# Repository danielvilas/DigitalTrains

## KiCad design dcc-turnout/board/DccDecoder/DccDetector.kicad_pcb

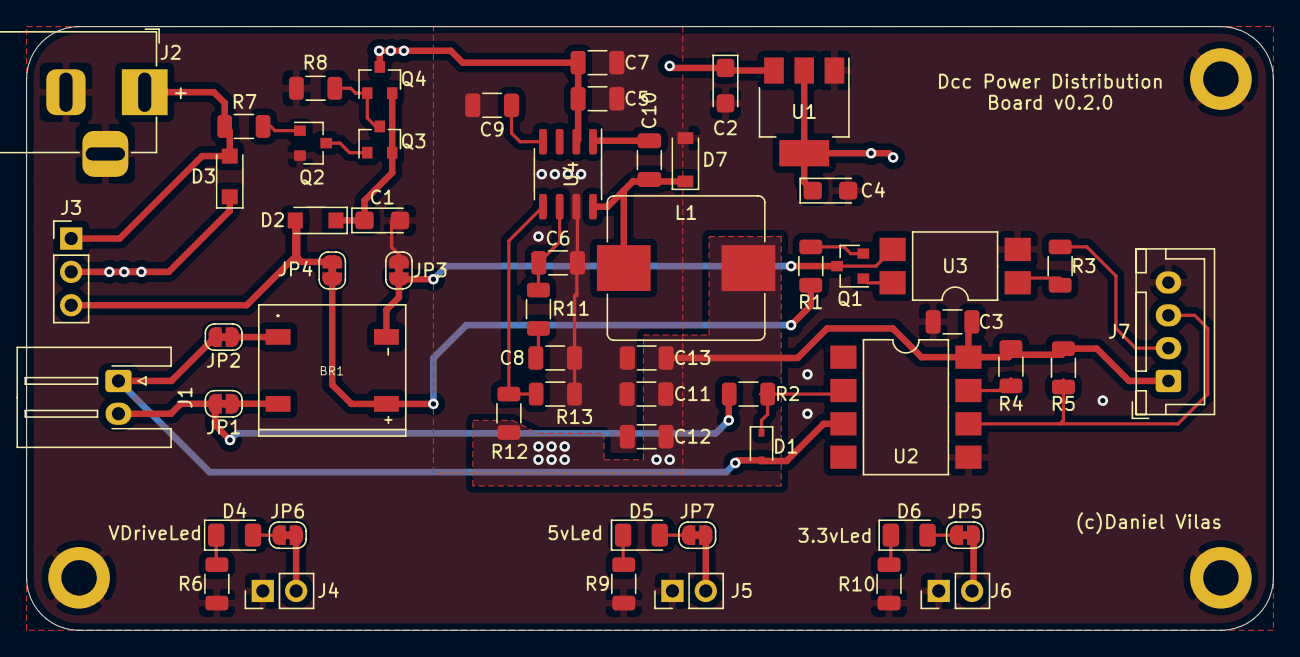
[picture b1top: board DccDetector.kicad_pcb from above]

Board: 4 copper layers, 95.0 x 46.0 mm, 60 parts (0 on the bottom side), 35 nets.

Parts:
BR1: DB107S; DIOB_DB107S
C1, C2, C4: 10uf; CP_EIA-3216-18_Kemet-A
C3: 10uf; C_1206_3216Metric
C5, C7, C11, C12, C13: 10uf 2m; C_1206_3216Metric
C6: 10pf; C_1206_3216Metric
C8: 5.6nf; C_1206_3216Metric
C9: 8.2nf; C_1206_3216Metric
C10: 100nf 1m; C_1206_3216Metric
D1: 1N4148; D_SOD-323
D2, D3: GS1510FL; D_SOD-123FL
D4, D5, D6: LED; LED_1206_3216Metric
D7: SS24A+; D_SOD-123
H1, H2, H3: MountingHole_Pad; MountingHole_2.7mm_M2.5_DIN965_Pad
J1: Conn_01x02; JST_XH_S2B-XH-A-1_1x02_P2.50mm_Horizontal
J2: Conn_01x02; BarrelJack_Horizontal
J3: Conn_01x03; PinHeader_1x03_P2.54mm_Vertical
J4, J5, J6: Conn_01x02; PinHeader_1x02_P2.54mm_Vertical
J7: Conn_01x04; JST_XH_B4B-XH-A_1x04_P2.50mm_Vertical
JP1, JP2, JP3, JP4: Jumper_NC; SolderJumper-2_P1.3mm_Bridged_RoundedPad1.0x1.5mm
JP5, JP6, JP7: Jumper_2_Bridged; SolderJumper-2_P1.3mm_Bridged_RoundedPad1.0x1.5mm
L1: 22uH 75mO; L_Bourns_SRP1035
Q1: BC857; SOT-23
Q2: BC817; SOT-23
Q3: BC807; SOT-23
Q4: BSS308; SOT-23
R1, R10: 100; R_1206_3216Metric
R2: 3k; R_1206_3216Metric
R3: 1K; R_1206_3216Metric
R4, R5: 10K; R_1206_3216Metric
R6: 900; R_1206_3216Metric
R7, R8: 100K; R_1206_3216Metric
R9: 200; R_1206_3216Metric
R11: 5.62K; R_1206_3216Metric
R12: 10.2K; R_1206_3216Metric
R13: 1.96K; R_1206_3216Metric
U1: AMS1117-3.3; SOT-223-3_TabPin2
U2: 6N137S1; SMDIP-8_W9.53mm
U3: PC817; SMDIP-4_W9.53mm
U4: TPS54331D; SOIC-8_3.9x4.9mm_P1.27mm

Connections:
+3V3: C4.1, J6.2, JP5.2, U1.2
+5V: C2.1, C3.1, C11.1, C12.1, C13.1, J5.2, J7.1, JP7.2, L1.2, R4.2, R5.2, R12.1, U1.3, U2.8
/Dcc Interface/DccP+: BR1.+, JP4.1, R1.2
/Dcc Interface/DccP-: BR1.-, JP3.1, Q1.3, U3.3
/Dcc Interface/DccPower: D2.2, J3.3, JP4.2
/Dcc Interface/J: J1.2, JP1.2, R2.2
/Dcc Interface/J_ACK: BR1.~, JP1.1
/Dcc Interface/K: D1.2, J1.1, JP2.2, U2.3
/Dcc Interface/K_ACK: BR1.~., JP2.1
/Power Distribution/Vin: D3.2, J2.1, J3.1, R7.2
/Power Distribution/_BOOT: C10.1, U4.1
/Power Distribution/_DccVinP: C1.1, D2.1, Q3.2, Q4.2
/Power Distribution/_PH: C10.2, D7.1, L1.1, U4.8
/_ack: J7.2, R3.1
/_dcc: J7.3, R5.1, U2.6
GND: C1.2, C2.2, C3.2, C4.2, C5.2, C6.2, C7.2, C8.2, C9.2, C11.2, C12.2, C13.2, D7.2, H1.1, H2.1, H3.1, J2.2, J2.3, J4.1, J5.1, J6.1, J7.4, JP3.2, Q2.2, R6.2, R8.2, R9.2, R10.2, R13.2, U1.1, U2.5, U3.2, U4.7
unnamed: C6.1, R11.1, U4.6
unnamed: C8.1, R11.2
unnamed: C9.1, U4.4
unnamed: D1.1, R2.1, U2.2
unnamed: D4.1, R6.1
unnamed: D4.2, JP6.1
unnamed: D5.1, R9.1
unnamed: D5.2, JP7.1
unnamed: D6.1, R10.1
unnamed: D6.2, JP5.1
unnamed: Q1.1, U3.4
unnamed: Q1.2, R1.1
unnamed: Q2.1, R7.1
unnamed: Q2.3, Q3.1
unnamed: Q3.3, Q4.1, R8.1
unnamed: R3.2, U3.1
unnamed: R4.1, U2.7
unnamed: R12.2, R13.1, U4.5
Vdrive: C5.1, C7.1, D3.1, J3.2, J4.2, JP6.2, Q4.3, U4.2

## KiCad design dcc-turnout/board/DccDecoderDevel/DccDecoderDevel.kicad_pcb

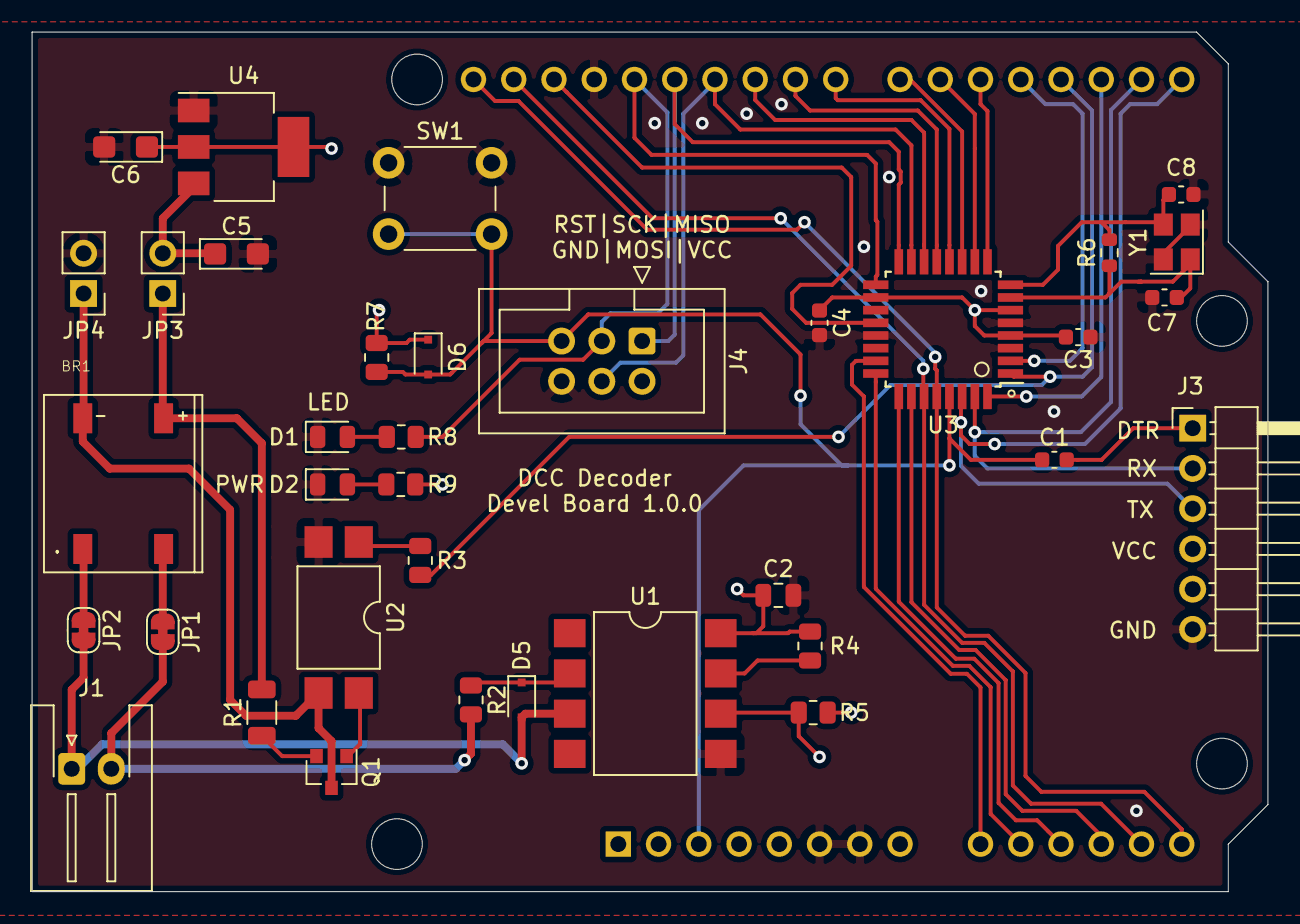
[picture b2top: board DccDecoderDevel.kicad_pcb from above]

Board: 4 copper layers, 78.0 x 54.2 mm, 37 parts (1 on the bottom side), 41 nets.

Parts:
A1: Arduino_UNO_R3; Arduino_UNO_R3_WithMountingHoles
BR1: DB107S; DIOB_DB107S
C1, C3, C4: 100nf; C_0603_1608Metric
C2: 10uf; C_0805_2012Metric
C5, C6: 10uf; CP_EIA-3216-18_Kemet-A
C7, C8: 22pf; C_0603_1608Metric
D1, D2: LED; LED_0805_2012Metric
D5: 1N4148; D_SOD-323F
D6: CD1206-S01575; D_SOD-323F
J1: Conn_01x02; JST_XH_S2B-XH-A-1_1x02_P2.50mm_Horizontal
J3: Conn_01x06; PinHeader_1x06_P2.54mm_Horizontal
J4: ICSP; IDC-Header_2x03_P2.54mm_Vertical
JP1, JP2: Jumper_NC_Small; SolderJumper-2_P1.3mm_Bridged_RoundedPad1.0x1.5mm
JP3, JP4: Jumper_NO; PinHeader_1x02_P2.54mm_Vertical
Q1: BC560; SOT-23
R1: 100; R_1206_3216Metric
R2: 3k; R_0805_2012Metric
R3: 1K; R_0805_2012Metric
R4, R5, R7, R8, R9: 10K; R_0805_2012Metric
R6: 1M; R_0603_1608Metric
SW1: SW_Push; SW_PUSH_6mm_H4.3mm
U1: 6N137; SMDIP-8_W9.53mm
U2: PC817; SMDIP-4_W9.53mm
U3: ATmega328P-AU; TQFP-32_7x7mm_P0.8mm
U4: AMS1117-5.0; SOT-223-3_TabPin2
Y1: Crystal_GND24; Crystal_SMD_3225-4Pin_3.2x2.5mm

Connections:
+12V: A1.8, C5.1, JP3.2, U4.3
/A0: A1.9, U3.23
/A1: A1.10, U3.24
/A2: A1.11, U3.25
/A3: A1.12, U3.26
/A4: A1.13, A1.31, U3.27
/A5: A1.14, A1.32, U3.28
/AREF: A1.30, U3.20
/D2: A1.17, R5.1, U1.6, U3.32
/D3: A1.18, R3.1, U3.1
/D4: A1.19, U3.2
/D5: A1.20, U3.9
/D6: A1.21, U3.10
/D7: A1.22, U3.11
/D8: A1.23, U3.12
/D9: A1.24, U3.13
/D10: A1.25, U3.14
/D11: A1.26, J4.4, U3.15
/D12: A1.27, J4.1, U3.16
/D13: A1.28, J4.3, R8.2, U3.17
/DTR: C1.2, J3.1
/Dcc-Interface/DCC_A: J1.2, JP1.2, R2.2
/Dcc-Interface/DCC_B: D5.2, J1.1, JP2.2, U1.3
/Dcc-Interface/J_ACK: BR1.~, JP1.1
/Dcc-Interface/K_ACK: BR1.~., JP2.1
/FTDI_RX: A1.16, J3.2, U3.31
/FTDI_TX: A1.15, J3.3, U3.30
/RST: A1.3, C1.1, D6.2, J4.5, R7.2, SW1.2, U3.29
GND: A1.6, A1.7, A1.29, C2.2, C3.1, C4.2, C5.2, C6.2, C7.1, C8.1, D1.1, D2.1, J3.6, J4.6, JP4.2, SW1.1, U1.5, U2.2, U3.3, U3.5, U3.21, U4.1, Y1.2, Y1.4
unnamed: BR1.+, JP3.1, R1.2
unnamed: BR1.-, JP4.1, Q1.3, U2.3
unnamed: C7.2, R6.1, U3.7, Y1.1
unnamed: C8.2, R6.2, U3.8, Y1.3
unnamed: D1.2, R8.1
unnamed: D2.2, R9.1
unnamed: D5.1, R2.1, U1.2
unnamed: Q1.1, U2.4
unnamed: Q1.2, R1.1
unnamed: R3.2, U2.1
unnamed: R4.1, U1.7
VCC: A1.2, A1.5, C2.1, C3.2, C4.1, C6.1, D6.1, J3.4, J4.2, R4.2, R5.2, R7.1, R9.2, U1.8, U3.4, U3.6, U3.18, U4.2

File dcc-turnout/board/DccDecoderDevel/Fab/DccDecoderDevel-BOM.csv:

Comment,Designator,Footprint,LCSC, LCSC, MANUFACTURER
"Arduino_UNO_R3","A1","Module:Arduino_UNO_R3_WithMountingHoles",""
"DB107S","BR1","Project:DIOB_DB107S","","C5377","Rectron Semiconductor"
"100nf","C1,C4,C3","Capacitor_SMD:C_0603_1608Metric","","C14663",""
"10uf","C2","Capacitor_SMD:C_0805_2012Metric","","C15850",""
"10uf","C6,C5","Capacitor_Tantalum_SMD:CP_EIA-3216-18_Kemet-A",""," C7171",""
"22pf","C7,C8","Capacitor_SMD:C_0603_1608Metric","","C1653",""
"LED","D2,D1","LED_SMD:LED_0805_2012Metric","","C2296",""
"1N4148","D5","Diode_SMD:D_SOD-323F","","C2128",""
"CD1206-S01575","D6","Diode_SMD:D_SOD-323F",""," C2128",""
"Conn_01x02","J1","Connector_JST:JST_XH_S2B-XH-A-1_1x02_P2.50mm_Horizontal",""
"Conn_01x06","J3","Connector_PinHeader_2.54mm:PinHeader_1x06_P2.54mm_Horizontal",""
"ICSP","J4","Connector_IDC:IDC-Header_2x03_P2.54mm_Vertical",""
"Jumper_NC_Small","JP1,JP2","Jumper:SolderJumper-2_P1.3mm_Bridged_RoundedPad1.0x1.5mm",""
"Jumper_NO","JP4,JP3","Connector_PinHeader_2.54mm:PinHeader_1x02_P2.54mm_Vertical",""
"BC560","Q1","Package_TO_SOT_SMD:SOT-23","","C8326",""
"100","R1","Resistor_SMD:R_1206_3216Metric","","C17901",""
"3k","R2","Resistor_SMD:R_0805_2012Metric","","C17661",""
"1K","R3","Resistor_SMD:R_0805_2012Metric","","C17513",""
"1M","R6","Resistor_SMD:R_0603_1608Metric",""," C22935",""
"10K","R9,R8,R4,R5,R7","Resistor_SMD:R_0805_2012Metric","","C17414",""
"SW_Push","SW1","Button_Switch_THT:SW_PUSH_6mm_H4.3mm",""
"6N137","U1","Package_DIP:SMDIP-8_W9.53mm","","C110020",""
"PC817","U2","Package_DIP:SMDIP-4_W9.53mm","","C106900",""
"ATmega328P-AU","U3","Project:TQFP-32_7x7mm_P0.8mm","","C14877",""
"AMS1117-5.0","U4","Package_TO_SOT_SMD:SOT-223-3_TabPin2","","C6187",""
"Crystal_GND24","Y1","Crystal:Crystal_SMD_3225-4Pin_3.2x2.5mm","","C13738",""

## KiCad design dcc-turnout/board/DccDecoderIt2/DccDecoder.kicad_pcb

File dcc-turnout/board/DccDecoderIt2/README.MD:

# Dcc Decoder
This is a Dcc Decoder Module to move a turnout with a Servo

> __WARN__: this folder is a second iteration, to try to model PCB different. and check with version is more addecuate
>
> After testing some iterations only one will be on the repository.

## Desired Specs Status
* ̣[x]Remove Power Distribution to project:  [Power Distribution](../DccBlocks/DccPowerDistribution/)
* [ ] 2 Outputs for LEDs Aspects, to Vin
* [ ] 1 Rele Ouput (5V or 0)
* [x] UART for advanced configuration
* [x] Configure Pins
  * [ ] CV Program to advanced CF
    * [ ] POM if possible
  * [ ] Config mode to capture dcc Address
  * [x] Advanced config mode (2 packets, CV, value)
* [x] Reset Button
* [x] Programing port
  * [ ] Bootloader for uart if possible
  * [ ] if possible no BootX pins
* [x] I2C for EzyBus

## Power Design
First is to determine the power requirments of the diferent main sections, wihch are:

|       |min|expected|max|notes|
|---    |--:|--:|--:|---|
|Servo  | 5 |150|800|idle, run, stall|
|Leds   |10 |20 |40 | underlight, 1led, Both|
|Rele   |0  |80 |100| off, std, +margins|
|MCU    |20 |80 |120|STM32 minum, arduino expected[(1)](https://www.gadgetmakersblog.com/power-consumption-arduinos-atmega328-microcontroller/), +margin|
|Others |10|50|60| extra margins
|**Sum**|45|**380**|*1020*|

In the reality, the max compsution of the servo (Stall) may only occurr when the user is setting up the device. So with this information we can design our power stage, from VDrive to 5V using "WEBENCH Power Designer" indicating we want **1 AMP output** wiht nominal output of **500mA**

## ChangeLog
### v0.1.0
* Initial Version
### v0.2.0
* [x] Buck Converter
* [x] Power Switch with mosfet
### v0.3.0
* [X] D1 FootPrint
* [x] D7 Check stock and review footprint
* [x] Output Connectors, following amps and voltage
* [x] Check 12v DC Jack size with layout
* [X] J7 (Dcc iface) horizontal
* [X] J7 Silk explanation
* [x] J1,J2 and J3, place a bit low and add Mount Hole
* [x] J1,J2 and J3, explain in silk.
* [x] JP* (all) explain in silk (back)
* [x] Dcc iface add jumper Normally Open to isolate 5v rail from buck
* [x] Copy design to new Project (Dcc Power Distributor)
## v0.4.0
* [x] Remove Power Distritubion
* [x Basic MCU
  * [x] MCU
  * [x] SWD
  * [x] Boot 0
* [x] UART.
* [x] I2C
* [x] LEDS
* [x] RELE
* [x] Servo
  * [ ] full
  * [x] enabled
* [x] Config Pins

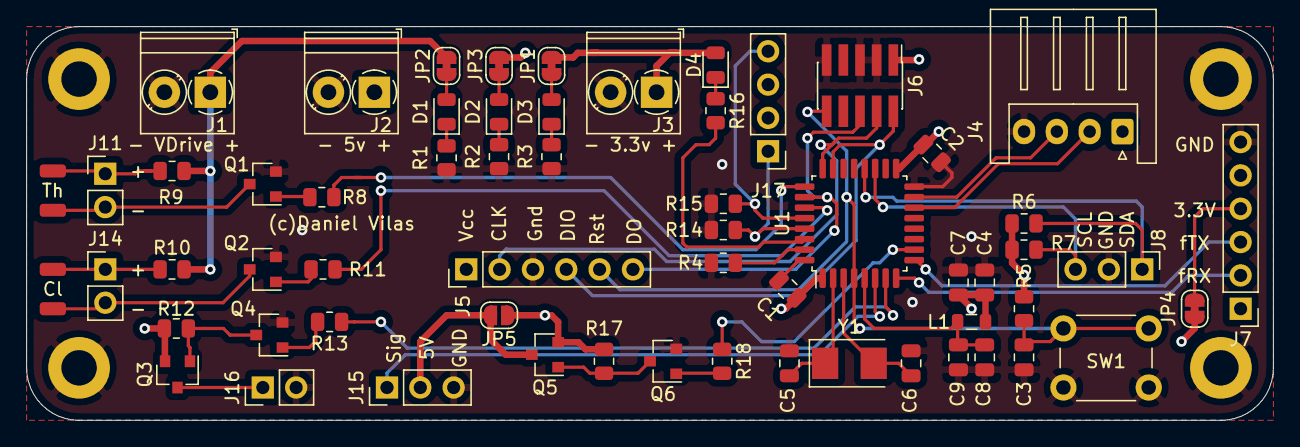
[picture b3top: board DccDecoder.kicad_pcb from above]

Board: 4 copper layers, 95.0 x 30.0 mm, 67 parts (0 on the bottom side), 46 nets.

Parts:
C1, C2, C3: 100nf; C_0805_2012Metric
C4, C8: 1uF; C_0805_2012Metric
C5, C6: 20pf; C_0805_2012Metric
C7, C9: 10nF; C_0805_2012Metric
D1, D2, D3, D4: LED; LED_0805_2012Metric
H1, H2, H3, H4: MountingHole_Pad; MountingHole_2.7mm_M2.5_DIN965_Pad
J1, J2, J3: Conn_01x02; TerminalBlock_Phoenix_PT-1,5-2-3.5-H_1x02_P3.50mm_Horizontal
J4: Conn_01x04; JST_XH_S4B-XH-A_1x04_P2.50mm_Horizontal
J5, J7: Conn_01x06; PinHeader_1x06_P2.54mm_Vertical
J6: Conn_02x05 Odd_Even; PinHeader_2x05_P1.27mm_Vertical_SMD
J8, J15: Conn_01x03; PinHeader_1x03_P2.54mm_Vertical
J9, J10, J12, J13: Conn_01x01; SolderWirePad_1x01_SMD_1x2mm
J11, J14, J16: Conn_01x02; PinHeader_1x02_P2.54mm_Vertical
J17: Conn_01x04; PinHeader_1x04_P2.54mm_Vertical
JP1, JP2, JP3, JP4: Jumper_2_Bridged; SolderJumper-2_P1.3mm_Bridged_RoundedPad1.0x1.5mm
JP5: Jumper_2_Open; SolderJumper-2_P1.3mm_Open_RoundedPad1.0x1.5mm
L1: 10uH; L_0805_2012Metric
Q1, Q2, Q4, Q6: AO3400A; SOT-23
Q3, Q5: AO3401A; SOT-23
R1, R6, R7, R8, R9, R10, R11, R12, R13, R14, R15, R17, R18: 1K; R_0805_2012Metric
R2: 200; R_0805_2012Metric
R3, R16: 100; R_0805_2012Metric
R4, R5: 10K; R_0805_2012Metric
SW1: SW_Push; SW_PUSH_6mm
U1: STM32F030K6Tx; LQFP-32_7x7mm_P0.8mm
Y1: 8MHz; Crystal_SMD_5032-2Pin_5.0x3.2mm

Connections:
+3V3: C1.2, C2.2, C4.1, C7.1, D4.2, J3.1, J5.1, J6.1, J17.2, J17.3, JP1.2, JP4.2, L1.2, R5.1, R6.1, R7.1, U1.1, U1.17
+5V: J2.1, J4.1, JP3.2, JP5.1, Q3.2, Q5.2, R12.2, R17.2
/CfgAdvanced: J17.4, R15.2, U1.28
/CfgBasic: J17.1, R14.2, U1.29
/CfgStatus: R16.2, U1.30
/ClosedLed: R11.1, U1.27
/F_RX: J7.2, U1.8
/F_TX: J7.3, U1.9
/F_Vcc: J7.4, JP4.1
/Out Puts/_ServoPwr: J15.2, JP5.2, Q5.3
/ReleEn: R13.1, U1.7
/SCL: J8.3, R7.2, U1.19
/SDA: J8.1, R6.2, U1.20
/ServoEn: R18.1, U1.10
/ServoSig: J15.1, U1.6
/ThrownLed: R8.1, U1.25
/_ack: J4.2, U1.14
/_dcc: J4.3, U1.15
/uC 030K6/BOOT0: R4.1, U1.31
/uC 030K6/NRST: C3.1, J5.5, J6.10, R5.2, SW1.1, U1.4
/uC 030K6/PA13: J5.4, J6.2, U1.23
/uC 030K6/PA14: J5.2, J6.4, U1.24
/uC 030K6/PB3: J5.6, J6.6, U1.26
/uC 030K6/PF0: C5.1, U1.2, Y1.1
/uC 030K6/PF1: C6.1, U1.3, Y1.2
/uC 030K6/_VDDA: C8.1, C9.1, L1.1, U1.5
GND: C1.1, C2.1, C3.2, C4.2, C5.2, C6.2, C7.2, C8.2, C9.2, H1.1, H2.1, H3.1, H4.1, J1.2, J2.2, J3.2, J4.4, J5.3, J6.3, J6.5, J6.9, J7.6, J8.2, J15.3, J16.2, Q1.2, Q2.2, Q4.2, Q6.2, R1.2, R2.2, R3.2, R4.2, R14.1, R15.1, SW1.2, U1.16, U1.32
unnamed: D1.1, R1.1
unnamed: D1.2, JP2.1
unnamed: D2.1, R2.1
unnamed: D2.2, JP3.1
unnamed: D3.1, R3.1
unnamed: D3.2, JP1.1
unnamed: D4.1, R16.1
unnamed: J10.1, J11.2, Q1.3
unnamed: J9.1, J11.1, R9.1
unnamed: J12.1, J14.1, R10.1
unnamed: J13.1, J14.2, Q2.3
unnamed: J16.1, Q3.3
unnamed: Q1.1, R8.2
unnamed: Q2.1, R11.2
unnamed: Q3.1, Q4.3, R12.1
unnamed: Q4.1, R13.2
unnamed: Q5.1, Q6.3, R17.1
unnamed: Q6.1, R18.2
Vdrive: J1.1, JP2.2, R9.2, R10.2

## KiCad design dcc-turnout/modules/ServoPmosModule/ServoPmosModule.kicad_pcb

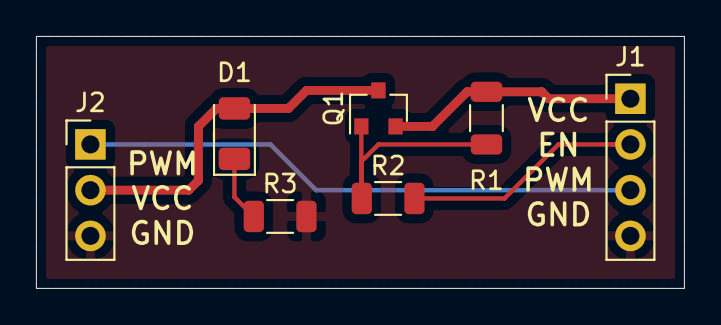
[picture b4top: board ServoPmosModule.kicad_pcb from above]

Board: 2 copper layers, 36.0 x 14.0 mm, 7 parts (0 on the bottom side), 7 nets.

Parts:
D1: LED; LED_1206_3216Metric
J1: Conn_01x04; PinHeader_1x04_P2.54mm_Vertical
J2: Conn_01x03; PinHeader_1x03_P2.54mm_Vertical
Q1: Q_PMOS_GSD; SOT-23
R1: 10K; R_1206_3216Metric
R2, R3: 1K; R_1206_3216Metric

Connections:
/pwm: J1.3, J2.1
/pwr_en: J1.2, R2.2
/pwr_in: J1.1, Q1.2, R1.1
/pwr_out: D1.2, J2.2, Q1.3
GND: J1.4, J2.3, R3.2
unnamed: D1.1, R3.1
unnamed: Q1.1, R1.2, R2.1
